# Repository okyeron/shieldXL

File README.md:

# shieldXL

A rework/remix of the monome norns shield - an open-source/DIY shield for Raspberry Pi boards, providing hardware compatibility with the [norns](https://monome.org/docs/norns) ecosystem. Original designed by monome (brian crabtree, aka @tehn). Remixed in spring 2023 by denki-oto.

__Please be very aware that this project is not directly supported by [monome](https://monome.org). Do not email monome asking for build help, debugging or repairs__

## specifications

- audio codec: CS4270  
- audio jacks: 6.5mm in and out, line level  
- OLED: NHD-2.7-12864WDW3-M (w/ MOLEX connector)  
- 3x pushbutton switches, 3x rotary encoders  
- dimensions (with enclosure): 138mm x 96mm x 30mm  

## versions

__shieldXL 20230423__
This rework/remix is based on the 210330 version of the norns shield. It uses the same disk image as the 210330 shield with the cs4270 codec.

## documentation

[See the monome website for general norns shield documentation](https://monome.org/docs/norns/shield/) 

## build

[Bill of Materials](bom/BOM.md)

[Build Guide](BUILD.md)

## installation

See [https://monome.org/docs/norns/help/#fresh-shield](https://monome.org/docs/norns/help/#fresh-shield) for installation instructions.  

See [norns releases on github](https://github.com/monome/norns-image/releases/tag/231114-img) for disk images (pre-211028 shield for cs4270 codec).   

Pi3 disk image:    
*  [norns231114-shield-pi3](https://github.com/monome/norns-image/releases/download/231114-img/norns231114-shield-pi3-cs4720.tgz)

Pi4 disk images (Try starting with 220306. If you get a blank screen, try starting over with 231114):  
* Pi4 220306 [norns220306-shield-pi4](https://github.com/monome/norns-image/releases/download/220306/norns220306-shield-pi4-cs4270.tgz)  
* Pi4 231114 [norns231114-shield-pi4](https://github.com/monome/norns-image/releases/download/231114-img/norns231114-shield-pi4-cs4720.tgz)  

REMEMBER TO EXPAND THE DISK IMAGE AFTER INSTALL  
[https://monome.org/docs/norns/shield/#expand-filesystem](https://monome.org/docs/norns/shield/#expand-filesystem)

## enabling hardware midi

```
cd ~
git clone https://github.com/okyeron/shieldXL.git
cd ~/shieldXL 
./install-midi.sh
```
(note - the install script will trigger a reboot)  

Then Edit `/boot/config.txt` 

`sudo nano /boot/config.txt`  

scroll to the bottom of the text and add the following at the end  
 
```
enable_uart=1
dtoverlay=miniuart-bt
dtoverlay=uart0
dtoverlay=midi-uart0
```
Then edit `/boot/cmdline.txt` 

`sudo nano /boot/cmdline.txt`  

and remove `serial0`    
(so change `console=serial0,115200` to `console=115200`)  
and `sudo reboot`  

This will internally connect the shieldXL hardware TRS MIDI jacks to the "Virtual MIDI" port which is accessible from the norns MIDI menu (SYSTEM>DEVICES>MIDI).  

__MIDI Troubleshooting__   

- When checking MIDI functionality, remember that MIDI OUT has a Type A/B switch on the bottom front edge of the main PCB. Try switching that if you're not getting MIDI to your device.

## mods

__Battery Modication__  
Add a Pisugar S Plus battery to your shieldXL:  https://github.com/JGuzak/shieldXl_battery  

## general troubleshooting

- Most soldering problems can be solved simply by reheating solder joints. Bad solders can result in various problems: screen doesn't turn on, knobs/keys don't work.
- Use a good SD card, not a cheap one. If you're having trouble, try using a different card.
- Be sure to use the correct power supply. The pi will not power well from a laptop and you'll get confusing errors. Get a dedicated 3A USB supply, or very high output USB battery.
- see the [norns documentation](https://monome.org/docs/norns/shield/) for help with the software  

## notes

- The shield does not have a dedicated headphone output, but headphones work fine on the main outputs (use the left output jack). The headphone gain level within the norns menu does nothing in this case.
- The battery indication will not function - there is no battery.

## License

[GNU GENERAL PUBLIC LICENSE](LICENSE.txt)

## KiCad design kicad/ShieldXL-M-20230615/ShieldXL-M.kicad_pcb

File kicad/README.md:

# shieldXL 

Designed with [Kicad 8](https://www.kicad.org/)  

ShieldXL-M-20230615  

Based on the 210330 norns shield designed by monome. Remixed/redesigned march 2023 by steven noreyko/denki-oto.  

No official support - do not ask monome for help.   

Kicad files are provided "as-is". Pull requests or modifications to the original repository will not be accepted. No support/assistance can be provided for ordering or building PCBs from these files.

Open Source Hardware GPLv3.  See LICENSE.txt for details.

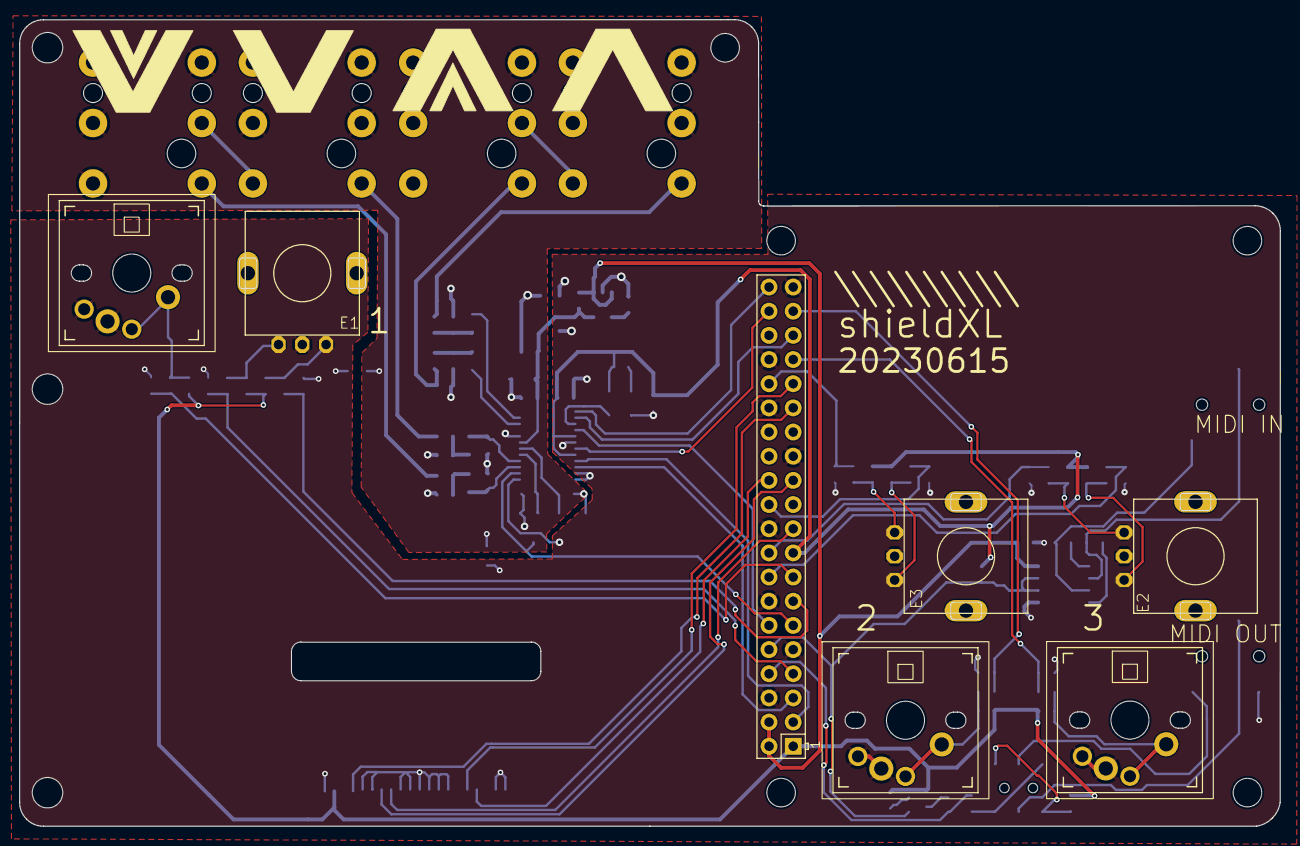
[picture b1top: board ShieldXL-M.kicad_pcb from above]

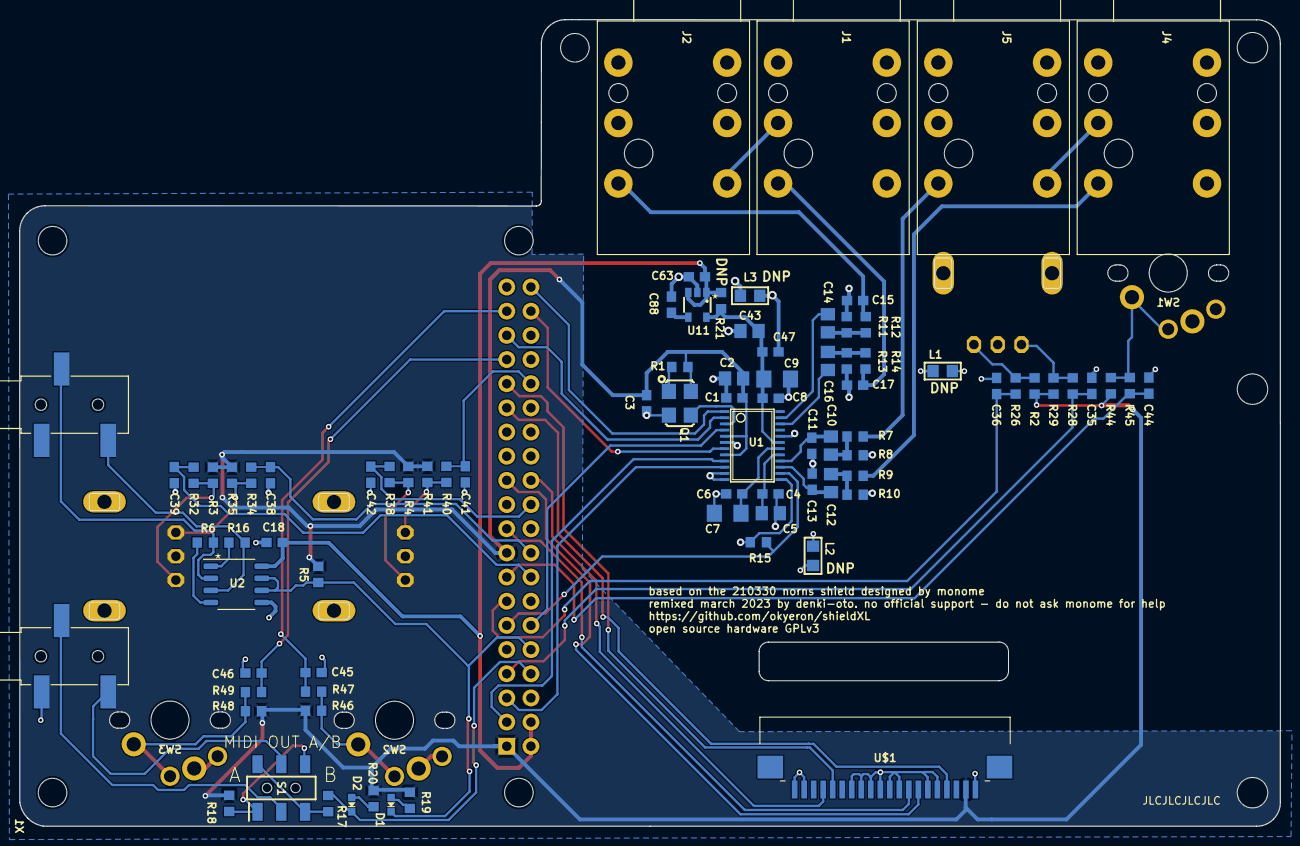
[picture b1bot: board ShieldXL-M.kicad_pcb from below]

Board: 2 copper layers, 132.5 x 84.8 mm, 91 parts (84 on the bottom side), 66 nets.

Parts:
C1, C4, C6, C8, C18, C47, C63: 100n; C0603
C2, C5, C10, C12, C43: 10u; C0805
C3, C35, C36, C38, C39, C41, C42, C44, C45, C46, C88: 10n; C0603
C7, C9: 47u; C1206
C11, C13: 220p COG; C0603
C14, C16: 3.3u; C0805
C15, C17: 2700p COG; C0603
D1: RED; CHIPLED_0603_NOOUTLINE
D2: BLUE; CHIPLED_0603_NOOUTLINE
E1, E2, E3: ENC; PEC11RN
J1, J2, J4, J5: NRJ6HF; Jack_6.35mm_Neutrik_NRJ6HF_Horizontal
J3, J6: PJ-320B; LUOYANG-DISHANG_PJ-320B
L1, L2: DNP; L0805
L3: FERRITE; L0805
Q1: ASFL1-12.288MHZ-LCS-T; ASF
R1, R2, R3, R4, R8, R10, R11, R13, R15, R26, R28, R29, R32, R34, R35, R38, R40, R41, R44, R45, R46, R47, R48, R49: 10k; R0603
R5: 470Ω; R0603
R6, R16: 220Ω; R0603
R7, R9: 4.99k; R0603
R12, R14: 590; R0603
R17, R18, R19: 47Ω; R0603
R20: 15Ω; R0603
R21: DNP; R0603
S1: EG1390B; SOP250P600X400-6N
SW1, SW2, SW3: PVA1; Choc_MX_combo
U1: CS4270; TSSOP24
U2: HCPL-0631-500E; SSOP-8_3.9x5.05mm_P1.27mm
U11: TPS793475DBVR; SSOP5
U$1: OLED128X64; F-FPC1M20P-B310
X1: RASPI_BOARD_B+#_E3; RASPI_BOARD_B+_EDGES_3DRILL

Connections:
+3V3: C1.1, C2.1, C3.1, Q1.4 (VCC), R1.1, R2.2, R3.2, R4.2, R5.2, R18.2, R19.2, R20.2, R29.2, R35.2, R41.2, R44.1, R46.1, R48.1, U1.5 (VD), U1.8 (VLC), U$1.2 (VDD), X1.1 (3V3A), X1.17 (3V3B)
+5V: C18.2, C63.1, R21.1, U2.8 (VCC), U11.1 (IN), U11.3 (EN), X1.2 (5V0A), X1.4 (5V0B)
/norns-shield-210330_1/A5V: C8.1, C9.1, C43.1, C47.1, R21.2, U1.19 (VA), U11.6 (OUT)
/norns-shield-210330_1/INA: C10.1, C11.1, U1.16 (AINB)
/norns-shield-210330_1/INB: C12.1, C13.1, U1.15 (AINA)
/norns-shield-210330_1/LRCK: U1.2 (LRCK), X1.35 (GPIO19)
/norns-shield-210330_1/MCLK: Q1.3 (FO), U1.3 (MCLK)
/norns-shield-210330_1/OUTA: C14.1, U1.23 (AOUTB)
/norns-shield-210330_1/OUTB: C16.1, U1.22 (AOUTA)
/norns-shield-210330_1/R-CODEC: R15.1, U1.14 (_RST), X1.11 (GPIO17)
/norns-shield-210330_1/SCL: U1.10 (CCLK), X1.5 (SCL)
/norns-shield-210330_1/SCLK: U1.4 (SCLK), X1.12 (GPIO18)
/norns-shield-210330_1/SDA: U1.9 (CDOUT), X1.3 (SDA)
/norns-shield-210330_1/SDIN: U1.1 (SDIN), X1.40 (GPIO21)
/norns-shield-210330_1/SDOUT: U1.7 (SDOUT), X1.38 (GPIO20)
/norns-shield-210330_2/RING1_4: R18.1, S1.1, S1.4
/norns-shield-210330_2/TIP1_5: R17.1, S1.3, S1.6
A1: C35.1, R28.2, X1.7 (GPIO04)
A2: C38.1, R34.2, X1.18 (GPIO24)
A3: C41.1, R40.2, X1.32 (GPIO12)
AGND: C4.2, C5.2, C6.2, C7.2, C8.2, C9.2, C11.2, C13.2, C15.2, C17.2, C47.2, J1.S, J2.R, J2.S, J4.RN, J4.S, J4.TN, J5.R, J5.RN, J5.S, L1.1, L2.1, L3.1, R8.2, R10.2, R11.2, R13.2, U1.20 (AGND)
B1: C36.1, R26.2, X1.13 (GPIO27)
B2: C39.1, R32.2, X1.16 (GPIO23)
B3: C42.1, R38.2, X1.22 (GPIO25)
CE0: U$1.17 (/CS), X1.24 (SPI_CE0)
GND: C1.2, C2.2, C3.2, C18.1, C35.2, C36.2, C38.2, C39.2, C41.2, C42.2, C43.2, C44.2, C45.2, C46.2, C63.2, C88.2, E1.GND, E2.GND, E3.GND, J3.4 (SLEEVE), L1.2, L2.2, L3.2, Q1.2 (GND), R15.2, SW1.SW2 (PIN-2), SW2.SW2 (PIN-2), SW3.SW2 (PIN-2), U1.6 (DGND), U1.11 (CS), U1.12 (CDIN), U1.13 (AD2), U2.5 (GND), U11.2 (GND), U$1.1 (VSS), U$1.5 (R/W), U$1.6 (E), U$1.9 (DB2), U$1.10 (DB3), U$1.11 (DB4), U$1.12 (DB5), U$1.13 (DB6), U$1.14 (DB7), U$1.19 (BS1), U$1.20 (BS0), X1.6 (GND_A), X1.9 (GND_B), X1.14 (GND_C), X1.20 (GND_D), X1.25 (GND_E), X1.30 (GND_F), X1.34 (GND_G), X1.39 (GND_H)
K1: C44.1, R45.2, X1.15 (GPIO22)
K2: C45.1, R47.2, X1.37 (GPIO26)
K3: C46.1, R49.2, X1.33 (GPIO13)
MIDI_RX: D1.C, R5.1, U2.6 (VO2), U2.7 (VO1), X1.10 (RXD)
MIDI_TX: D2.C, R17.2, X1.8 (TXD)
MOSI: U$1.8 (SDIN), X1.19 (SPI_MOSI)
unnamed: C10.2, R7.1, R8.1
unnamed: C12.2, R9.1, R10.1
unnamed: C14.2, R11.1, R12.1
unnamed: C15.1, J2.T, R12.2
unnamed: C16.2, R13.1, R14.1
unnamed: C17.1, J1.T, R14.2
unnamed: D1.A, R19.1
unnamed: D2.A, R20.1
unnamed: E1.A, R28.1, R29.1
unnamed: E1.B, R2.1, R26.1
unnamed: E2.A, R34.1, R35.1
unnamed: E2.B, R3.1, R32.1
unnamed: E3.A, R40.1, R41.1
unnamed: E3.B, R4.1, R38.1
unnamed: J1.R, J2.TN
unnamed: J3.3 (RING), S1.2 (2_COM)
unnamed: J3.2 (TIP), S1.5 (5_COM)
unnamed: J4.R, J5.TN
unnamed: J4.T, R9.2
unnamed: J5.T, R7.2
unnamed: J6.3 (RING), R6.1, U2.2 (CATHODE_1)
unnamed: J6.2 (TIP), R16.1, U2.3 (CATHODE_2)
unnamed: Q1.1 (OE), R1.2
unnamed: R44.2, R45.1, SW1.SW1 (PIN-1)
unnamed: R46.2, R47.1, SW2.SW1 (PIN-1)
unnamed: R48.2, R49.1, SW3.SW1 (PIN-1)
unnamed: C6.1, C7.1, U1.18 (FILT+)
unnamed: C4.1, C5.1, U1.17 (VQ)
unnamed: R16.2, U2.1 (ANODE_1)
unnamed: R6.2, U2.4 (ANODE_2)
unnamed: C88.1, U11.4 (NR)
O_DC: U$1.4 (D/C), X1.29 (GPIO05)
O_RESET: U$1.16 (/RES), X1.31 (GPIO06)
SCK: U$1.7 (SCLK), X1.23 (SPI_SCLK)

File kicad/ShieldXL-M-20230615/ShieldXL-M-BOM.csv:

"Reference","Value","Datasheet","Footprint","Qty","DNP","#","Description"
"C1,C4,C6,C8,C18,C47,C63","100n","","ShieldXL:C0603","7","","1",""
"C2,C5,C10,C12,C43","10u","","ShieldXL:C0805","5","","2",""
"C3,C35,C36,C38,C39,C41,C42,C44,C45,C46,C88","10n","","ShieldXL:C0603","11","","3",""
"C7,C9","47u","","ShieldXL:C1206","2","","4",""
"C11,C13","220p COG","","ShieldXL:C0603","2","","5",""
"C14,C16","3.3u","","ShieldXL:C0805","2","","6",""
"C15,C17","2700p COG","","ShieldXL:C0603","2","","7",""
"D1","RED","","ShieldXL:CHIPLED_0603_NOOUTLINE","1","","8",""
"D2","BLUE","","ShieldXL:CHIPLED_0603_NOOUTLINE","1","","9",""
"E1,E2,E3","ENC","","ShieldXL:PEC11RN","3","DNP","10",""
"J1,J2,J4,J5","NRJ6HF","https://www.neutrik.com/en/product/nrj6hf","ShieldXL:Jack_6.35mm_Neutrik_NRJ6HF_Horizontal","4","","11",""
"J3,J6","PJ-320B","","ShieldXL:LUOYANG-DISHANG_PJ-320B","2","","12",""
"L1,L2,R21","DNP","","-- mixed values --","3","DNP","13",""
"L3","FERRITE","","ShieldXL:L0805","1","","14",""
"Q1","ASFL1-12.288MHZ-LCS-T","","ShieldXL:ASF","1","","15",""
"R1,R2,R3,R4,R8,R10,R11,R13,R15,R26,R28,R29,R32,R34,R35,R38,R40,R41,R44,R45,R46,R47,R48,R49","10k","","ShieldXL:R0603","24","","16",""
"R5","470Ω","","ShieldXL:R0603","1","","17",""
"R6,R16","220Ω","","ShieldXL:R0603","2","","18",""
"R7,R9","4.99k","","ShieldXL:R0603","2","","19",""
"R12,R14","590","","ShieldXL:R0603","2","","20",""
"R17,R18,R19","47Ω","","ShieldXL:R0603","3","","21",""
"R20","15Ω","","ShieldXL:R0603","1","","22",""
"S1","EG1390B","","ShieldXL:SOP250P600X400-6N","1","","23",""
"SW1,SW2,SW3","PVA1","","ShieldXL:Choc_MX_combo","3","DNP","24",""
"U$1","FPC1M20P-B310","","ShieldXL:F-FPC1M20P-B310","1","","25",""
"U1","CS4270","","ShieldXL:TSSOP24","1","","26",""
"U2","HCPL-0631-500E","","ShieldXL:SSOP-8_3.9x5.05mm_P1.27mm","1","","27",""
"U11","TPS793475DBVR","","ShieldXL:SSOP5","1","","28",""
"X1","RASPI_BOARD_B+#_E3","","ShieldXL:RASPI_BOARD_B+_EDGES_3DRILL","1","DNP","29",""

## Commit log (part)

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2023-06-06 bom update
2023-06-08 Explain alternative display cable in BOM.
2023-06-10 fix midi-install path
2023-06-10 fix permissions
2023-06-10 update readme with midi install details
2023-06-11 start on build notes
2023-06-11 change case to enclosure
2023-06-15 add inkline
2023-06-15 FPC cable info
2023-06-15 Update BOM.md
    typo
2023-06-15 Update BOM.md
    formatting
2023-06-16 add 3d case models
2023-06-28 add 1.4.3 case files
2023-07-11 bom/doc updates
2023-07-11 typo
2023-07-11 link additions
2023-07-12 add dimensions
2023-07-13 remove 1.2 update readme
2023-07-13 add positioning tips
2023-07-17 Fix SVG and add DXF
2023-07-17 redo svg
2023-07-25 Update BOM.md
    add part number for plastic jack nuts
2023-08-03 Add images to build guide, add build guide and bill of materials links to README.md
2023-08-05 Update BOM.md
    add detail for thread size
2023-08-19 add battery mod link
2023-09-03 add new case STL
2023-10-02 Restart ttymidi0 automatically when it crashes
    Unfortunately, it isn't very stable at the moment.
2023-10-02 update case files, readme
2023-12-18 Update README.md
    update for new disk images
2023-12-19 add case v1.6.1
2024-01-12 reorganize top panels
2024-03-26 suggest norns231114-shield-pi4 for raspberry pi 4
    updating to this version worked for my raspberry pi 4b
2024-03-26 Update README.md
    add notes about pi4 disk images
2024-03-27 Update BOM.md
    add yellow display part number
2024-03-27 Update BOM.md
    fix display link
2024-04-27 add new case files
2024-11-12 Update install-midi.sh
    fix for breaking changes on new amidiminder updates.
    Use old stable version
2025-01-30 update build and add shieldsaver stls
2025-01-30 add shieldsaver photo
2025-01-30 add SLS STL picture
2025-01-30 update shieldsaver image
2025-01-30 fix stls
2025-02-27 update bom spreadsheets
